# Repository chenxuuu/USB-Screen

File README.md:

# USB-Screen

低成本PC资源监控小屏幕。如果感兴趣，点个星星呗。

PC monitor screen, only cost $5.

> only Chinese readme now.

## 硬件

- 主控：CH551
- 屏幕：1.4寸IPS彩屏
- 接口：microUSB、typec、排针
- 外壳：3d打印

## 使用的开发软件/框架

- 硬件设计：KICAD
- 嵌入式软件：标准C51 (Keil/SDCC)
- 外壳：OpenSCAD
- PC客户端：WPF (.net framework 4.0)
  - 可根据通讯协议自行开发客户端

## 通讯协议

目前通过`USB CDC`进行通讯。

设备插入后，会被识别为串口设备，设备实例路径为`USB\VID_1A86&PID_5722\ST1E6DIPSF0F0SPI3`

数据包分为两种：

### 包长度小于64字节

这种类型的数据包，将作为`刷新区域设置`+`像素信息`使用，刷新区域的范围为**0~239**，格式如下：

```txt
     1byte         1byte        1byte        1byte         1byte
+-------------+-------------+-----------+--------------+------------+
| data length | width start | width end | height start | height end |
+-------------+-------------+-----------+--------------+------------+
       ↓
|<--length-------------------------------......-->|
        1byte                1byte
+-------------------+------------------+------
| rgb565 high 8 bit | rgb565 low 8 bit |......
+-------------------+------------------+------
```

像素数据顺序为从左至右从上至下刷新，每个像素点的颜色为2字节，遵循`rgb565`色彩格式，如下

```txt
    1byte       1byte
+-----------+-----------+
| rrrr rggg | gggb bbbb |
+-----------+-----------+
```

#### `data length`的使用特例

因为`data length`包最长也只能为`59`，所以进行了额外定义：

1. `data length`的值为`0xC0`为亮度调节命令，后接1byte亮度参数，用于调节屏幕背光亮度
```txt
    1byte       1byte
+-----------+------------+
| 1100 0000 | brightness |
+-----------+------------+
```

2. `data length`的最高位`0x80`如果为1，则表示当前模式为黑白模式，此模式下1字节代表8个像素点，设备会将所有数据按黑白模式进行处理

3. `data length`的倒数第二高位`0x40`如果为1，则表示后面的数据全部为像素数据，同时`data length`剩下字节表示后面跟随数据的长度，注意总包长度必须小于64字节

```txt
     1byte
+---------------+
| 0x40 & length |
+---------------+
           ↓
|<-------length-----------------------......-->|
        1byte                1byte
+-------------------+------------------+------
| rgb565 high 8 bit | rgb565 low 8 bit |......
+-------------------+------------------+------
```

### 包长度等于64字节

64字节数据将全部作为像素数据发送至屏幕

```txt
        1byte               1byte              1byte               1byte
+-------------------+------------------+-------------------+------------------+---
| rgb565 high 8 bit | rgb565 low 8 bit | rgb565 high 8 bit | rgb565 low 8 bit |...
+-------------------+------------------+-------------------+------------------+---
```

## 功能

PC控制端正在制作中

欢迎[提建议](https://github.com/chenxuuu/USB-Screen/issues)或直接参与开发。

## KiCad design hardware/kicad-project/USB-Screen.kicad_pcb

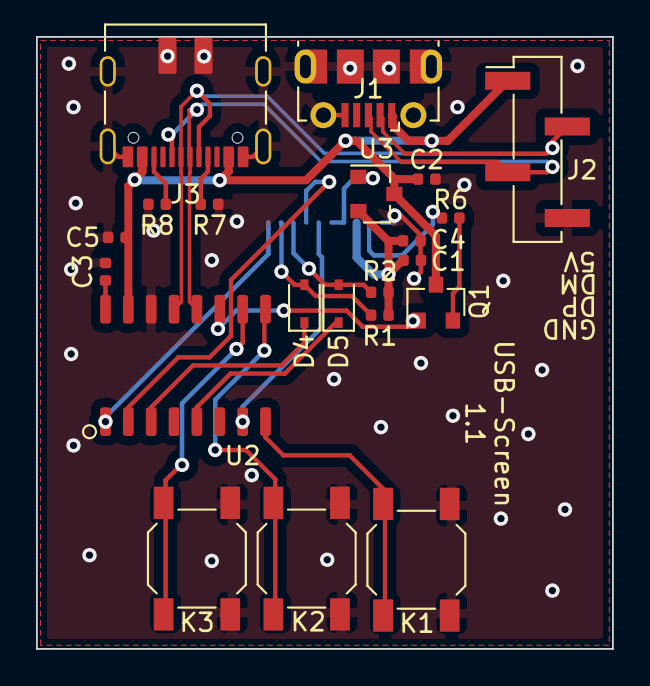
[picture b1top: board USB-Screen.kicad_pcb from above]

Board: 2 copper layers, 32.0 x 34.0 mm, 22 parts (1 on the bottom side), 21 nets.

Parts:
C1, C3, C5: 0.1uF; C_0402_1005Metric
C2, C4: 1uF; C_0402_1005Metric
D4, D5: 1n4148; D_SOD-323
J1: USB_B_Micro; USB_Micro-B_Molex-105017-0001
J2: Conn_01x04; PinHeader_1x04_P2.54mm_Vertical_SMD_Pin1Left
J3: USB_C_Receptacle_USB2.0; USB_C_Receptacle_Steady_UTC16-G
K1, K2, K3: SW_4*4mm; SW_Push_1P1T_NO_4x4mm_H2.0mm
Q1: NPN; SOT-23
R1, R2: 10K; R_0402_1005Metric
R6: 33R; R_0402_1005Metric
R7, R8: 5.1K; R_0402_1005Metric
U1: ZJY154T-PG04
U2: CH551; SOP-16_4.55x10.3mm_P1.27mm
U3: SC662; SOT-23

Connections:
+3V3: C1.2, C4.1, R1.1, R2.2, U1.4, U3.2
+5V: C2.1, C5.1, J1.1, J2.1, J3.A4, J3.A9, J3.B4, J3.B9, Q1.3, U2.15, U3.3
/CS: U1.8, U2.2
/DC: U1.7, U2.7
/K1: K1.1, U2.8
/K2: K2.1, U2.9
/K3: K3.1, U2.10
/KEDA: R6.1, U1.3
/PWM: Q1.1, U2.11
/RST: U1.11, U2.1
/SCL: D5.2, R2.1, U1.9
/SDA: D4.2, R1.2, U1.10
/USB_D+: J1.3, J2.3, J3.A6, J3.B6, U2.12
/USB_D-: J1.2, J2.2, J3.A7, J3.B7, U2.13
GND: C1.1, C2.2, C3.1, C4.2, C5.2, J1.5, J1.6, J2.4, J3.A1, J3.A12, J3.B1, J3.B12, J3.S1, K1.2, K2.2, K3.2, R7.1, R8.2, U1.1, U1.2, U1.5, U1.6, U1.12, U2.14, U3.1
unnamed: C3.2, U2.16
unnamed: D4.1, U2.3
unnamed: D5.1, U2.5
unnamed: J3.A5, R7.2
unnamed: J3.B5, R8.1
unnamed: Q1.2, R6.2

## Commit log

2020-09-15 完成原理图
2020-09-15 pcb完成
2020-09-15 微调，打样
2020-09-18 补上两个头文件
2020-09-18 上传pdf手册
2020-09-22 先把示例代码搬过来
2020-09-22 spi代码也抄过来，待改
2020-09-23 上传3d外壳模型大体形状，待改
2020-09-27 我也不知道为啥屏幕不亮，先把代码传上来
2020-09-28 屏幕能量了，但是亮度好低
2020-09-28 hid发spi数据
2020-09-28 简单描述协议
2020-09-28 更正背光电路
2020-09-29 稍微改改初始化参数，优化下屏幕效果
2020-09-29 新建一个pc端项目
2020-09-29 简单测试hid收发
2020-09-29 不知道为啥显示效果不对，明天再调
2020-09-30 用软件spi才能用这屏
2020-09-30 可以显示图片了
2020-09-30 加个进度条
2020-09-30 干掉窗口边框
2020-09-30 事件绑定与UI分离
2020-09-30 优化逻辑，提升刷屏速度到10秒左右
2020-10-01 修改 .gitignore规则
2020-10-05 修改过滤规则,并添加bootloader和新的Firmvare工程
2020-10-05 上位机勉强能用了
2020-10-05 上位机可选使用硬件SPI还是软件SPI,上位机添加固件更新功能.
2020-10-05 屏蔽输出反馈的数据
2020-10-05 下位机启用4路端口接收数据
2020-10-05 调整下位机SPI代码
2020-10-05 硬件SPI初始化屏幕成功
2020-10-06 使用4通道HID传输数据,速度大有改善!
2020-10-06 整理工程结构,将HID驱动的显示屏工程单独存放
2020-10-06 修复数据卡死后无法更新固件的BUG
2020-10-06 添加数据传输耗时统计
2020-10-06 过滤无关的HID设备插拔事件,防止干扰.
2020-10-07 使下位机反馈完整数据(开销忽略不计)
2020-10-07 使用线程安全的队列,以解决偶尔出现的取值null问题.
2020-10-07 使用异步多线程发送数据,提升效率(虽然看不出什么卵用)
2020-10-08 更正编译报错
2020-10-09 检查数据包同步标志
2020-10-09 USBCDC模式传输数据,大幅提升速度. 刷屏一页耗时0.4s
2020-10-10 调整硬件SPI上拉电压,解决硬SPI刷屏闪烁问题.
2020-10-10 sda、clk加上拉电阻，去掉下载电路焊盘
2020-10-10 修改CDC配置以使用SPI外部上拉
2020-10-10 提交HID+CDC调试工具
2020-10-10 C# 串口发送不出去数据,找不到原因.
2020-10-10 串口代码能用
2020-10-10 老代码挪个地方
2020-10-10 解决主机获取字符串描述符失败的BUG PS:是由于指针类型不一致导致的(编译器竟然不报错)
2020-10-10 调整测试代码,临时解决数据错位的问题.
2020-10-10 添加测试用数据
2020-10-11 再次提升CDC通信速度,现在刷屏只需要0.3s内.
2020-10-11 初步调通上位机,勉强能用了.
2020-10-11 调整工程目录结构,方便管理
2020-10-11 删除未用的头文件引用
2020-10-11 添加一个简易实现的持续截图推送功能(资源占用巨大)
2020-10-12 更改spi外设逻辑，稍微提高效率
2020-10-12 解决上位机频繁截图会导致资源消耗过大的问题.
2020-10-12 再次提升刷屏效率，现在可以达到0.19s/帧
2020-10-12 修改SPI总线分压电路
2020-10-12 优化SPI逻辑，提升SPI速度
2020-10-12 给电路图添加多种备用调试方案
2020-10-12 调整外设初始化顺序
2020-10-12 用二极管实现电平转换
2020-10-12 重新布线
2020-10-12 IO初始化逻辑还是改回去吧。。。
2020-10-12 外壳的大概样子
2020-10-12 修改通讯协议,再次提升效率,现在刷新1帧只需要0.165s左右
2020-10-13 加上盖子
2020-10-13 感觉没什么提升空间了,551的SPI速度太拉跨了.
2020-10-13 更改目录结构
2020-10-13 盖子改得规则一点
2020-10-13 修改注释
2020-10-13 优化内存使用，减少GC发生率
2020-10-13 下位机添加黑白模式
2020-10-13 对中途拔出串口进行处理,避免程序崩溃.
2020-10-13 二极管换成小封装的
2020-10-13 拔出usb后不需要关闭串口.
2020-10-13 Create main.yml
    测试Actions自动编译
2020-10-13 微调外壳
2020-10-13 修改上位机的事务逻辑,好像变方便了一点? 虽然代码有点混乱,后面再优化吧.
2020-10-14 加上typec座
2020-10-14 更改pcb布局
2020-10-14 三个led改成按键
2020-10-14 完善readme
2020-10-14 readme 需要严谨一点.
2020-10-14 调整变量声明
2020-10-14 添加一个debug信息打印点
2020-10-15 cpp的东西都删了，让GitHub能正常识别
2020-10-15 编译时移除未使用的函数
2020-10-15 添加俩个3D封装
2020-10-15 添加自定义3D模型
2020-10-15 3d模型
2020-10-15 更正拼写错误
2020-10-15 Update main.yml
    仅修改上位机部分代码后才编译
2020-10-16 加上通讯协议解释
2020-10-16 更正笔误
2020-10-16 笔误x2
2020-10-16 换成微软官方的msbuild环境
2020-10-16 pr也加上
2020-10-16 加上固件的ci
2020-10-16 更正ci
2020-10-16 测试下ci
2020-10-17 修复usb协议栈的bug
2020-10-17 修改默认波特率参数(好像并没有用)
2020-10-17 修改编译优化等级Lv9
2020-10-17 修改端点报告周期和USB协议版本 然而还是没能找到USBCDC连接HUB竟然比直连PC速度更快的原因.
2020-10-17 修改Bootloader控制命令
2020-10-18 完成CDCBootloader
2020-10-18 更正函数名称
2020-10-18 CDCBootloader 设备描述符
2020-10-18 BootloaderCDC初步测试能用了 可能丢包,需要添加反馈命令超时判断.
2020-10-19 行增数据长度1-62的发包模式(不携带命令),使用D6位作为识别.
2020-10-19 修复一个指令位定义搞反了的bug
2020-10-19 修复取数据指针问题.
2020-10-20 测试刷屏库
2020-10-20 修复黑白模式的取指针BUG
2020-10-20 修复黑白模式,移位寄存器未赋值的bug
2020-10-20 双色图像显示功能
2020-10-20 更新协议解释
2020-10-20 屏幕类的数据绑定处理
2020-10-20 稍微改改
2020-10-20 文件夹名字改一下
2020-10-20 简单摆了点东西
2020-10-21 串口断开自动重连逻辑
2020-10-21 界面摆一摆
2020-10-21 dll插件加载与例子
2020-10-21 启动自动连接上次串口，预览图实时更新
2020-10-21 调整usb协议栈
2020-10-21 插件已经能跑，预览图不正常
2020-10-22 简化字符串格式化
2020-10-22 使屏幕内容可以正常预览
2020-10-23 标题栏跟随系统颜色
2020-10-23 调整列表获取逻辑
2020-10-23 调整图片颜色数据的处理方式
2020-10-23 设备断开后停止刷新数据
2020-10-23 修改窗口样式
2020-10-23 实现例子插件功能
2020-10-23 修正图片长宽写反了的BUG
2020-10-23 试试彩虹渐变,看起来不错.
2020-10-23 添加指针时钟插件
2020-10-24 稍微美化时钟
2020-10-24 解决插件重复调用导致的Bitmap多线程冲突问题。
2020-10-24 修改变量为属性
2020-10-24 给时钟添加文字信息
2020-10-24 优化图像处理性能
2020-10-24 解除对Dll的锁定,载入dll后可以删除文件.
2020-10-25 时针半透明处理,这样可以透出下方的文字.
2020-10-25 PCB直插方案
2020-10-25 规范插件命名规则 #主类#副类#次类#编号#
2020-10-26 修改插件风格
2020-10-26 修改文件名称
2020-10-26 添加新的时钟插件(可使用外部PNG主题资源)
2020-10-26 调整客户端UI参数
2020-10-26 新插件功能,调用外部图片绘制时钟
2020-10-30 删除未用的函数参数
2020-11-11 添加亮度调节命令
2020-11-11 增加亮度控制功能
2020-11-11 修复亮度调节命令穿插在数据命令之中会导致花屏的BUG
2020-11-11 使用0xC0作为亮度调节命令
2020-11-12 优化代码结构,压缩hex体积.
2020-11-12 改0402封装为0603封装,对手工焊接更友好.
2020-11-12 设置Gerber生成配置
2022-06-23 Bump Newtonsoft.Json in /ProjectCDC/Client/UsbScreen
    Bumps [Newtonsoft.Json](https://github.com/JamesNK/Newtonsoft.Json) from 12.0.3 to 13.0.1.
    - [Release notes](https://github.com/JamesNK/Newtonsoft.Json/releases)
    - [Commits](https://github.com/JamesNK/Newtonsoft.Json/compare/12.0.3...13.0.1)
    ---
    updated-dependencies:
    - dependency-name: Newtonsoft.Json
2022-10-10 Add Plug to read infos from aida64
2023-03-19 Update README.md
    增加亮度指令说明
2024-10-28 update: 我也不知道改了啥
2025-01-02 add: 几个新文件
